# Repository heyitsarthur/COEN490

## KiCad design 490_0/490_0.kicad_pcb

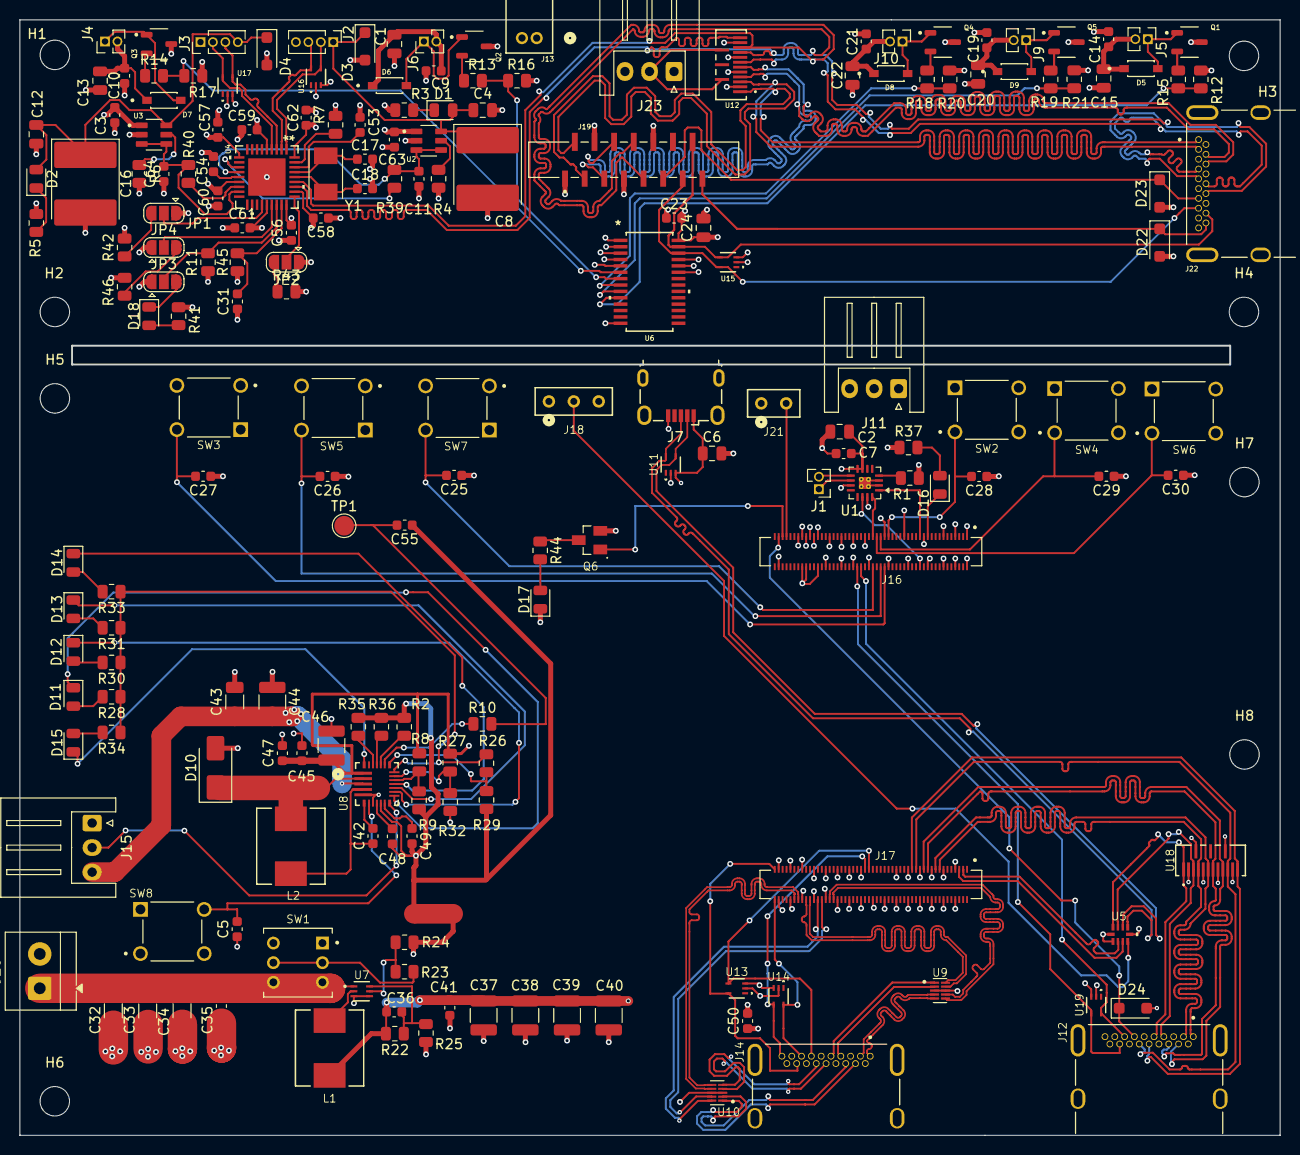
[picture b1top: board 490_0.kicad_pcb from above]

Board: 4 copper layers, 128.5 x 113.7 mm, 200 parts (0 on the bottom side), 147 nets.

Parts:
C1, C2, C4, C6, C12, C13, C15, C20, C22, C24: 10u; C_0805_2012Metric
C3, C5, C7, C9, C10, C11, C14, C19, C21, C23, C25, C26, C27, C28, C29, C30, C31, C35, C41, C42, C49, C53, C54, C55, C56, C57, C58, C59, C60, C61, C63, C64: 100n; C_0603_1608Metric
C8, C16: 120u; CP_EIA-7260-38_AVX-R_HandSolder
C17, C18, C36: 33pF; C_0603_1608Metric
C32, C33, C34: 10u; C_1206_3216Metric
C37, C38, C39, C40, C44, C46: 22u; C_1210_3225Metric
C43: 1u; C_1206_3216Metric
C45, C47, C50: 4.7u; C_0603_1608Metric
C48, C62: 1u; C_0603_1608Metric
D1, D2: LTST-C170TBKT; LED_0805_2012Metric
D3, D4: SMF5.0A; D_SOD-123F
D5, D6, D7, D8, D9: 1N4148W; SODFL3816X120N
D10: B330B-13-F; D_SMA
D11, D12, D13, D14, D16, D18: LTST-C170GKT; LED_0805_2012Metric
D15: LTST-C170YKT; LED_0805_2012Metric
D17: LTST-C170KRKT; LED_0805_2012Metric
D22, D23, D24: GSMF3.3A; D_SOD-123F
H1, H2, H3, H4, H5, H6, H7, H8: MountingHole; MountingHole_3mm
J1, J4, J5, J6, J9, J10: PAD; PinHeader_1x02_P1.27mm_Vertical
J2, J3: PAD; PinHeader_1x04_P1.27mm_Vertical
J7: 629105150521; USB_Micro-B_Wuerth_629105150521
J11, J15, J23: S3B-XH-A; JST_XH_S3B-XH-A_1x03_P2.50mm_Horizontal
J12, J14, J22: 2000-1-1-20-00-BK; CNCTECH_2000-1-1-20-00-BK
J13: S2B-ZR; CONN_S2B-ZR_JST
J16, J17: DF40HC(3.0)-100DS-0.4V(58); HIROSE_DF40C-100DS-0.4V_51_
J18: TS-103-G-A; CON3_1X3_TU_HTS_SAI - 3POS Connector
J19: SFW15S-2STE1LF
J20: YO0201500000G; TerminalBlock_4Ucon_1x02_P3.50mm_Horizontal
J21: TS-102-G-A; CON2_1X2_TU_HTS_SAI
JP1, JP2, JP3, JP4: SolderJumper-3_P1.3mm_Open_RoundedPad1.0x1.5mm
L1, L2: 2.2u; IND_SRP6540-2R2M_BRN
NT2: NetTie_2; NetTie-2_SMD_Pad2.0mm
Q1, Q2, Q3, Q4, Q5: AO3400A; SOT95P280X125-3N
Q6: BSS84; SOT95P240X120-3N
R1, R15, R16, R17, R20, R21, R23, R39, R40: 100k; R_0805_2012Metric
R2, R36: 215k; R_0805_2012Metric
R3, R5: 1k; R_0805_2012Metric
R4, R6: 20k; R_0805_2012Metric
R7: 12k; R_0805_2012Metric
R8: 76.8k; R_0805_2012Metric
R9: 24.3k; R_0805_2012Metric
R10, R26, R32, R42, R43, R45, R46: 10k; R_0805_2012Metric
R11: 330; R_0805_2012Metric
R12, R13, R14, R18, R19: 220; R_0805_2012Metric
R22: 220k; R_0805_2012Metric
R24: 30.1k; R_0805_2012Metric
R25: 30k; R_0805_2012Metric
R27: 27.4k; R_0805_2012Metric
R28, R30, R31, R33, R34, R41: 1.5k; R_0805_2012Metric
R29: 15k; R_0805_2012Metric
R35: 120k; R_0805_2012Metric
R37, R44: 470; R_0805_2012Metric
SW1: TL2230EEF140; SW_TL2230EEF140
SW2, SW3, SW4, SW5, SW6, SW7, SW8: TL1105LF160Q; SW_TL1105LF160Q
TP1: TestPoint; TestPoint_Pad_D2.0mm
U1: MAX98357A; TQFN-16-1EP_3x3mm_P0.5mm_EP1.23x1.23mm_ThermalVias
U2, U3: TPS2553DBVR; SOT95P280X145-6N_TPS2553DBVR
U4: USB2512B-I/M2; SQFN36_M2_MCH_USB2512B_I_M2
U5: TS3USB221AQRSERQ1; RSE10
U6: PCA9685; TSSOP28_SOT361-1_NXP
U7: TPS566247DRLR; SOT-5X3-6_DRL_TEX
U8: MP2639AGR-Z; IC26_MP2632BGR-Z_MNP
U9, U10: EMI8142MUTAG; SON40P220X135X50-10N_EMI8142MUTAG
U11, U13, U14, U15, U16, U17, U19: SP3003-02XTG; SOT553_LTF_SP3003_02XTG
U12, U18: TPD8S009DSMR
Y1: 24M20P2/XT324-10/10; Crystal_SMD_TXC_7A-2Pin_5x3.2mm

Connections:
+3.3V: J11.2, J12.18 (+5V), J16.78, J16.84, J16.86, J18.1, Q6.2 (S), R37.1, U5.10 (VCC), U18.13 (VCC), U18.15 (VCC), U19.3
+3.3V_GLASSES: C3.2 (-), C23.2 (-), C24.1 (+), C56.2 (-), C57.2 (-), C58.2 (-), C59.2 (-), C60.2 (-), C61.2 (-), C62.2 (-), C63.2 (-), J23.2, R41.1, R42.2, R43.2, R45.1, R46.2, U2.1 (IN), U3.1 (IN), U4.5 (VDDA33), U4.10 (VDDA33), U4.15 (VDD33), U4.23 (VDD33), U4.27 (VBUS_DET), U4.29 (VDDA33), U4.36 (VDDA33), U6.28 (VDD), U12.13 (VCC), U12.15 (VCC), U15.3
+5V: C2.1 (+), C7.2 (-), C36.2 (-), C37.2 (-), C38.2 (-), C39.2 (-), C40.2 (-), C41.2 (-), C50.1 (+), J11.3, J14.18 (+5V), J16.77, J16.79, J16.81, J16.83, J16.85, J16.87, L1.2, R1.1, R22.2, U1.7 (VDD), U1.8 (VDD), U13.3, U14.3
+5V_GLASSES: C1.1 (+), C9.2 (-), C10.2 (-), C13.1 (+), C14.2 (-), C15.1 (+), C19.2 (-), C20.1 (+), C21.2 (-), C22.1 (+), D5.1 (K), D6.1 (C), D7.1 (K), D8.1 (K), D9.1 (K), J4.2, J5.2, J6.2, J9.2, J10.2, J13.2, J23.3, U16.3, U17.3
+VBATT_7V4: C32.2 (-), C33.2 (-), C34.2 (-), C35.2 (-), J20.1, SW1.3 (C), SW1.6 (C), U7.1 (VIN)
/PCB1/PCB1-Board Connector A/CAM1_C_N: J12.12 (CK-), J17.27, U18.10 (D3+)
/PCB1/PCB1-Board Connector A/CAM1_C_P: J12.10 (CK+), J17.29, U18.12 (D3-)
/PCB1/PCB1-Board Connector A/CAM1_D0_N: J12.3 (D2-), J17.15, U18.4 (D1+)
/PCB1/PCB1-Board Connector A/CAM1_D0_P: J12.1 (D2+), J17.17, U18.6 (D1-)
/PCB1/PCB1-Board Connector A/CAM1_D1_N: J12.6 (D1-), J17.21, U18.7 (D2+)
/PCB1/PCB1-Board Connector A/CAM1_D1_P: J12.4 (D1+), J17.23, U18.9 (D2-)
/PCB1/PCB1-Board Connector A/Camera_GPIO: D24.1 (K), J12.13 (CEC), J16.97
/PCB1/PCB1-Board Connector A/HDMI0_CEC: J14.13 (CEC), J17.51, U13.4
/PCB1/PCB1-Board Connector A/HDMI0_CLK_N: J17.90, U10.6 (OUT_2-)
/PCB1/PCB1-Board Connector A/HDMI0_CLK_P: J17.88, U10.7 (OUT_2+)
/PCB1/PCB1-Board Connector A/HDMI0_HOTPLUG: J14.19 (HPD), J17.53, U14.4
/PCB1/PCB1-Board Connector A/HDMI0_SCL: J14.15 (SCL), J17.100, U14.5
/PCB1/PCB1-Board Connector A/HDMI0_SDA: J14.16 (SDA), J17.99, U13.5
/PCB1/PCB1-Board Connector A/HDMI0_TX0_N: J17.84, U9.10 (OUT_1+)
/PCB1/PCB1-Board Connector A/HDMI0_TX0_P: J17.82, U9.9 (OUT_1-)
/PCB1/PCB1-Board Connector A/HDMI0_TX1_N: J17.78, U10.10 (OUT_1+)
/PCB1/PCB1-Board Connector A/HDMI0_TX1_P: J17.76, U10.9 (OUT_1-)
/PCB1/PCB1-Board Connector A/HDMI0_TX2_N: J17.72, U9.6 (OUT_2-)
/PCB1/PCB1-Board Connector A/HDMI0_TX2_P: J17.70, U9.7 (OUT_2+)
/PCB1/PCB1-Board Connector A/PCM_CLK: J16.49, U1.16 (BCLK)
/PCB1/PCB1-Board Connector A/PCM_DOUT: J16.25, U1.1 (DIN)
/PCB1/PCB1-Board Connector A/PCM_FS: J16.26, U1.14 (LRCLK)
/PCB1/PCB1-Board Connector A/SCL1: J12.15 (SCL), J16.56, U19.5
/PCB1/PCB1-Board Connector A/SDA1: J12.16 (SDA), J16.58, U19.4
/PCB1/PCB1-Board Connector A/USB_N: J17.3, U5.7 (D-)
/PCB1/PCB1-Board Connector A/USB_P: J17.5, U5.8 (D+)
/PCB1/PCB1-Charging and Power Port + USB switch/MICROD+: J7.3 (D+), U5.1 (1D+), U11.5
/PCB1/PCB1-Charging and Power Port + USB switch/MICROD-: J7.2 (D-), U5.2 (1D-), U11.4
/PCB1/PCB1-Charging and Power Port + USB switch/USBhub_N: J12.9 (D0-), U5.4 (2D-), U18.1 (D0+)
/PCB1/PCB1-Charging and Power Port + USB switch/USBhub_P: J12.7 (D0+), U5.3 (2D+), U18.3 (D0-)
/PCB1/PCB1-HDMI/CLK+: J14.10 (CK+), U10.4 (IN_2+)
/PCB1/PCB1-HDMI/CLK-: J14.12 (CK-), U10.5 (IN_2-)
/PCB1/PCB1-HDMI/D0+: J14.7 (D0+), U9.2 (IN_1−)
/PCB1/PCB1-HDMI/D0-: J14.9 (D0-), U9.1 (IN_1+)
/PCB1/PCB1-HDMI/D1+: J14.6 (D1-), U10.2 (IN_1−)
/PCB1/PCB1-HDMI/D1-: J14.4 (D1+), U10.1 (IN_1+)
/PCB1/PCB1-HDMI/D2+: J14.3 (D2-), U9.4 (IN_2+)
/PCB1/PCB1-HDMI/D2-: J14.1 (D2+), U9.5 (IN_2-)
/PCB2/CK+: J19.9, J22.7 (D0+), J22.10 (CK+), U4.31 (USBDP_UP), U12.7 (D2+), U12.10 (D3+)
/PCB2/CK-: J19.8, J22.9 (D0-), J22.12 (CK-), U4.30 (USBDM_UP), U12.9 (D2-), U12.12 (D3-)
/PCB2/D0+: J19.3, J22.1 (D2+), U12.1 (D0+)
/PCB2/D0-: J19.2, J22.3 (D2-), U12.3 (D0-)
/PCB2/D1+: J19.6, J22.4 (D1+), U12.4 (D1+)
/PCB2/D1-: J19.5, J22.6 (D1-), U12.6 (D1-)
/PCB2/PCB2-PWM and Motors/I2C_SCL: J19.13, J22.15 (SCL), U6.26 (SCL), U15.5
/PCB2/PCB2-PWM and Motors/I2C_SDA: J19.14, J22.16 (SDA), U6.27 (SDA), U15.4
/PCB2/PCB2-PWM and Motors/PWM0: R14.2, R17.1, U6.6 (PWM0)
/PCB2/PCB2-PWM and Motors/PWM1: R13.2, R16.1, U6.7 (PWM1)
/PCB2/PCB2-PWM and Motors/PWM2: R18.2, R20.1, U6.8 (PWM2)
/PCB2/PCB2-PWM and Motors/PWM3: R19.2, R21.1, U6.9 (PWM3)
/PCB2/PCB2-PWM and Motors/PWM4: R12.2, R15.1, U6.10 (PWM4)
/PCB2/PCB2-USB 2.0 Bridge/D1+: J2.3, U4.2 (USBDP_DN1/PRT_DIS_P1), U16.5
/PCB2/PCB2-USB 2.0 Bridge/D1-: J2.2, U4.1 (USBDM_DN1/PRT_DIS_M1), U16.4
/PCB2/PCB2-USB 2.0 Bridge/D2+: J3.2, U4.4 (USBDP_DN2/PRT_DIS_P2), U17.5
/PCB2/PCB2-USB 2.0 Bridge/D2-: J3.3, U4.3 (USBDM_DN2/PRT_DIS_M2), U17.4
/PCB2/PCB2-USB 2.0 Bridge/EN1: R39.2, U4.12 (PRTPWR1/BC_EN1)
/PCB2/PCB2-USB 2.0 Bridge/EN2: R40.2, U4.16 (PRTPWR2/BC_EN2)
/PCB2/PCB2-USB 2.0 Bridge/nOCS1: C11.2 (-), R39.1, U2.3 (EN), U2.4 (~FAULT), U4.13 (OCS_N1)
/PCB2/PCB2-USB 2.0 Bridge/nOCS2: C64.2 (-), R40.1, U3.3 (EN), U3.4 (~FAULT), U4.17 (OCS_N2)
GND: C2.2 (-), C5.1 (+), C6.2 (-), C7.1 (+), C25.1 (+), C26.1 (+), C27.1 (+), C28.1 (+), C29.1 (+), C30.1 (+), C32.1 (+), C33.1 (+), C34.1 (+), C35.1 (+), C37.1 (+), C38.1 (+), C39.1 (+), C40.1 (+), C41.1 (+), C43.2 (-), C44.1 (+), C45.2 (-), C46.2 (-), C47.2 (-), C48.2 (-), C49.2 (-), C50.2 (-), C55.1 (+), D10.2 (A), D17.1 (K), D24.2 (A), J7.5 (GND), J7.6 (Shield), J11.1, J12.2 (D2S), J12.5 (D1S), J12.8 (D0S), J12.11 (CKS), J12.17 (GND), J12.SH1, J12.SH2, J12.SH3, J12.SH4, J14.2 (D2S), J14.5 (D1S), J14.8 (D0S), J14.11 (CKS), J14.17 (GND), J14.SH1, J14.SH2, J14.SH3, J14.SH4, J15.1, J16.1, J16.2, J16.7, J16.8, J16.13, J16.14, J16.22, J16.23, J16.32, J16.33, J16.42, J16.43, J16.52, J16.53, J16.59, J16.60, J16.65, J16.66, J16.71, J16.74, J16.98, J17.7, J17.8, J17.13, J17.14, J17.19, J17.20, J17.25, J17.26, J17.31, J17.32, J17.37, J17.38, J17.44, J17.50, J17.55, J17.56, J17.61, J17.62, J17.67, J17.68, J17.73, J17.74, J17.79, J17.80, J17.85, J17.86, J17.91, J17.92, J17.97, J17.98, J18.3, J20.2, J21.1, NT2.1, NT2.2, R2.1, R9.1, R24.1, R25.1, R29.1, R32.2, R35.1, R36.1, SW2.3, SW3.2, SW4.3, SW5.2, SW6.3, SW7.2, SW8.1, U1.2 (GAIN_SLOT), U1.3 (GND), U1.11 (GND), U1.15 (GND), U1.17 (PAD), U5.5 (GND), U5.6 (*OE), U7.3 (GND), U7.4 (AGND), U8.5 (PGND), U8.8 (MODE), U8.10 (AGND), U9.3 (VN), U9.8 (VN__1), U10.3 (VN), U10.8 (VN__1), U11.2, U13.2, U14.2, U18.2 (GND), U18.5 (GND), U18.8 (GND), U18.11 (GND), U19.2
GND_GLASSES: C1.2 (-), C3.1 (+), C4.2 (-), C8.2, C9.1 (+), C10.1 (+), C11.1 (+), C12.2 (-), C13.2 (-), C14.1 (+), C15.2 (-), C16.2, C17.2 (-), C18.2 (-), C19.1 (+), C20.2 (-), C21.1 (+), C22.2 (-), C23.1 (+), C24.2 (-), C31.1 (+), C53.1 (+), C54.1 (+), C56.1 (+), C57.1 (+), C58.1 (+), C59.1 (+), C60.1 (+), C61.1 (+), C62.1 (+), C63.1 (+), C64.1 (+), D3.2 (A), D4.2 (A), D22.2 (A), D23.2 (A), J2.4, J3.1, J13.1, J19.1, J19.4, J19.7, J19.10, J22.2 (D2S), J22.5 (D1S), J22.8 (D0S), J22.11 (CKS), J22.17 (GND), J22.SH1, J22.SH2, J22.SH3, J22.SH4, J23.1, JP1.1 (A), JP2.1 (A), JP3.1 (A), JP4.1 (A), Q1.3 (S), Q2.3 (S), Q3.3 (S), Q4.3 (S), Q5.3 (S), R3.1, R4.2, R5.1, R6.2, R7.2, R11.1, R15.2, R16.2, R17.2, R20.2, R21.2, U2.2 (GND), U3.2 (GND), U4.37 (VSS), U6.1 (A0), U6.2 (A1), U6.3 (A2), U6.4 (A3), U6.5 (A4), U6.14 (GND), U6.23 (#OE), U6.24 (A5), U6.25 (EXTCLK), U12.2 (GND), U12.5 (GND), U12.8 (GND), U12.11 (GND), U15.2, U16.2, U17.2
unnamed: C5.2 (-), SW8.3, U8.7 (PB)
unnamed: C17.1 (+), U4.33 (XTALIN/CLKIN), Y1.1
unnamed: C18.1 (+), U4.32 (XTALOUT), Y1.2
unnamed: C25.2 (-), J16.50, SW7.3
unnamed: C26.2 (-), J16.46, SW5.3
unnamed: C27.2 (-), J16.44, SW3.3
unnamed: C28.2 (-), J16.41, SW2.2
unnamed: C29.2 (-), J16.45, SW4.2
unnamed: C30.2 (-), J16.47, SW6.2
unnamed: C31.2 (-), R45.2, U4.26 (RESET_N)
unnamed: C36.1 (+), R22.1, R25.2, U7.6 (FB)
unnamed: C42.1 (+), U8.6 (BST)
unnamed: C42.2 (-), L2.1, U8.4 (SW)
unnamed: C43.1 (+), C44.2 (-), J15.3, U8.3 (VH)
unnamed: C48.1 (+), U8.9 (VCC)
unnamed: C49.1 (+), U8.11 (TMR)
unnamed: C53.2 (-), U4.34 (PLLFILT)
unnamed: C54.2 (-), U4.14 (CRFILT)
unnamed: C55.2 (-), R10.2, TP1.1
unnamed: D1.1 (K), R3.2
unnamed: D2.1 (K), R5.2
unnamed: D5.2 (A), J5.1, Q1.1 (D)
unnamed: D6.2 (A), J6.1, Q2.1 (D)
unnamed: D7.2 (A), J4.1, Q3.1 (D)
unnamed: D8.2 (A), J10.1, Q4.1 (D)
unnamed: D9.2 (A), J9.1, Q5.1 (D)
unnamed: D10.1 (K), L2.2, U8.2 (LX)
unnamed: D11.2 (A), R28.2
unnamed: D11.1 (K), U8.13 (LED1)
unnamed: D12.2 (A), R30.2
unnamed: D12.1 (K), U8.14 (LED2)
unnamed: D13.2 (A), R31.2
unnamed: D13.1 (K), U8.15 (LED3)
unnamed: D14.2 (A), R33.2
unnamed: D14.1 (K), U8.16 (LED4)
unnamed: D15.2 (A), R34.2
unnamed: D15.1 (K), U8.26 (CHG)
unnamed: D16.2 (A), R37.2
unnamed: D16.1 (K), J16.21
unnamed: D17.2 (A), R44.2
unnamed: D18.2 (A), R41.2
unnamed: D18.1 (K), JP3.3 (B)
unnamed: D22.1 (K), J19.15, J22.18 (+5V)
unnamed: D23.1 (K), J19.11, J22.13 (CEC)
unnamed: J1.1, U1.10 (OUTN)
unnamed: J1.2, U1.9 (OUTP)
unnamed: J15.2, U8.12 (MID)
unnamed: J18.2, U5.9 (S)
unnamed: J16.93, J21.2
unnamed: JP1.3 (B), R42.1
unnamed: JP1.2 (C), U4.22 (SDA/SMBDATA/NON_REM1)
unnamed: JP2.3 (B), R43.1
unnamed: JP2.2 (C), U4.28 (SUSP_IN/LOCAL_PWR/NON_REM0)
unnamed: JP3.2 (C), R11.2, U4.25 (HS_IND/CFG_SEL1)
unnamed: JP4.3 (B), R46.1
unnamed: JP4.2 (C), U4.24 (SCL/SMBCLK/CFG_SEL0)
unnamed: Q1.2 (G), R12.1
unnamed: Q2.2 (G), R13.1
unnamed: Q3.2 (G), R14.1
unnamed: Q4.2 (G), R18.1
unnamed: Q5.2 (G), R19.1
unnamed: Q6.3 (D), R44.1
unnamed: J16.95, Q6.1 (G)
unnamed: R23.2, SW1.2 (B), SW1.5 (B)
unnamed: R1.2, U1.4 (~SD_MODE)
unnamed: R4.1, U2.5 (ILIM)
unnamed: R6.1, U3.5 (ILIM)
unnamed: R7.1, U4.35 (RBIAS)
unnamed: R23.1, R24.2, U7.5 (EN)
unnamed: L1.1, U7.2 (SW)
unnamed: R8.1, R9.2, U8.17 (FB)
unnamed: R10.1, U8.21 (IB)
unnamed: R35.2, U8.24 (ILIM)
unnamed: R36.2, U8.23 (ISET)
unnamed: R26.1, R29.2, U8.20 (NTC)
unnamed: R2.2, U8.22 (OLIM)
unnamed: R27.2, R32.1, U8.18 (VLIM)
unnamed: R26.2, R28.1, R30.1, R31.1, R33.1, R34.1, U8.19 (VNTC)
VBUS1: C4.1 (+), C8.1, D1.2 (A), D3.1 (K), J2.1, U2.6 (OUT)
VBUS2: C12.1 (+), C16.1, D2.2 (A), D4.1 (K), J3.4, U3.6 (OUT)
VBUS_5V: C6.1 (+), C45.1 (+), C46.1 (+), C47.1 (+), J7.1 (VBUS), R8.2, R27.1, U8.1 (VL), U11.3

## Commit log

2025-11-20 Setup
2025-11-20 USB and POWER
2025-11-20 Startted power
2025-11-22 Added USB hub
2025-11-22 Added speakers, motors and started HDMI
2025-11-22 Power Supply
2025-11-23 Phase 2
2025-11-23 Added zip file of datasheets
2025-11-27 Small update
2025-11-27 Changed charging circuit
2025-11-27 Finished USB C charger (3.3 and 5V)
    Added buck converter after the charging IC for 3.3 and 5V outputs.
2025-11-30 Arranged schematic
    Added sheets (as in the phase 2 presentation)
2025-11-30 US letter format
2025-12-01 Changed some local labels to the right format
2025-12-01 Fixed buttons
2025-12-01 changed local labels
    Do not use global labels if its only used in a single sheet
2025-12-01 Added debouncing to the buttons
2025-12-12 Minor fixes
2025-12-12 LEDs for charger
2025-12-12 Charging circuit updates
    NTC thermal resistor
    Changed some TBD values for resistors and capacitors
2025-12-13 Changed the camera connectors
    - Added 2 and 4 lane MIPI 22 lane connectors
    - Added digikey link to a good type
2026-01-15 Minor updates + USB 2.0
2026-01-15 Minor updates
2026-01-19 USB2.0
    Added USB2.0 circuit
2026-01-19 Updated box diagram
2026-01-22 BOM + ESD replacement for HDMI
    Started BOM and changed ESD chips that were obsolete. Also added 2 pin connectors
2026-01-22 small commit
2026-01-23 Added another button + address fix
2026-01-27 Updated block diagram
2026-01-27 changed PCB block diagram
2026-01-28 Changed PCB block dagram and layout
2026-01-29 Schematic layout update
    - applied hierarchical labels
    - cleaned up the schematic
    - finalized CM4 connections
    - checked cm4 connections
2026-01-30 Cleaned up global labels
    TO DO: power chip change
2026-02-02 Updated power circuit
    We now have a 2 cell battery
    Chip provides 4A/5V source
2026-02-03 Finished power circuit
2026-02-05 Power + BOM update
2026-02-05 finished BOM
2026-02-06 Changed buck converter chip
2026-02-06 Updated the schematic
2026-02-09 Implemented Dmitry comments
2026-02-11 Final Fixes
2026-02-11 USB hub fix
2026-02-17 Implemented Dmitry recommendations
2026-02-20 Added datasheets and footprints to repo
2026-02-25 Implemented suggestions
    notes on schematics:
    Overall: Schematics needs to be improved, more compact and cleaner
    =========================
    I) on root page (page 1):
    overall: needs a bit of clean up of the diagram
    1. the diagram shows pcb3 and pcb1, but no pcb2, it is probably outdated and therefore might have errors in it, fix it to the latest version and rename things to reflect what it actually is. Also try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
2026-02-26 FFC to HDMI change
2026-02-27 Footprints
    Required library of custom footprints for the PCB design
2026-02-27 Reviewed BOM
    - changed some capacitors to a more fitting voltage rating
2026-02-27 Footprint Update
    1st half of footprints updated
2026-02-27 Footprint Update #2
    All footprints except for the capacitors have been attributed
2026-02-27 Archive update
    .zip files update for archive purposes
2026-03-03 ToF power routing
2026-03-03 Changed 8conn and BOM update
2026-03-03 PCB Trial Update
2026-03-03 LED names + 5V routing through ESD + renamed ESD chips to "U"
2026-03-03 Renamed crystal + BOM update
2026-03-03 Updated schematic PDF
2026-03-03 Changed ESD chip for HDMI
2026-03-03 Fixed capacitor symbols
2026-03-04 PCB Jumpstart
2026-03-04 Post-Dmitry Changes
2026-03-04 Added seperate ground for PWM motors
2026-03-04 Updated to 10 pin connector
2026-03-04 Added 10 pin connector footprint
2026-03-04 Changed footprints for pad connectors (for soldered components)
2026-03-04 Changed footprint for R4 and R6 to SMD
2026-03-04 Changed capacitor sizes
    🟢 Group 1: 100% Safe to Shrink to 0603These capacitors handle logic-level decoupling or high-frequency filtering on your 3.3V and 5V lines. Because the capacitance values are low (1µF or less), an 06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
2026-03-04 Assigned capacitor footprints
2026-03-04 Changed all the resistors to 0805 size
2026-03-04 Scheamtic update
2026-03-05 PCB_2 Design Initialization
2026-03-05 Added button debouncing
2026-03-05 changed power and ground symbols for glasses
2026-03-05 Generated BOM
2026-03-05 Changed audio chip to 5V
    It might pull to omuch if we ue the raspberry's 3.3V rail
2026-03-05 ERC check fix
2026-03-05 Updated scheamitc in folder
2026-03-05 Added side B for SW1
2026-03-05 switch fix
2026-03-05 Rerouted + external coponents update
2026-03-05 March 3rd
2026-03-06 PCB_Glasses Implementation
2026-03-06 15 pin connector mirrored
2026-03-06 Changed connector 15 pin
2026-03-07 Fixed button debouncing
2026-03-09 Git PCB Fix
2026-03-09 small push
2026-03-09 Some changes
2026-03-09 Placed 100 pin connectors
2026-03-09 Button debouncing fix
2026-03-10 started routing up to HDMI ESD impedance matching
2026-03-10 HDMI to ESD diff pairs routed
2026-03-10 Finished ESD diff pairs routing
2026-03-10 Changed microHDMI to normal HDMI because of the footprint
2026-03-10 Tuesday March 10th: 13:25
2026-03-10 Routing ESD to 100 pin connector
2026-03-10 Tuesday Match 10th: 14:45
    Conflicting skew fix
2026-03-10 Final push
2026-03-10 PCB merged, now schematic
2026-03-10 All merged up! 03-10
2026-03-10 Wired up screen HDMI to 100pin
2026-03-10 Still need to wire diff pairs from FFC HDMI
2026-03-11 Speaker circuit
2026-03-11 Routed the FFC HDMI to 100conn
2026-03-11 added a few grounds around signal vias
2026-03-11 Fixed SP3003-02XTG continuity
2026-03-11 Place CM4 footprint, starting to reroute everything
2026-03-11 Removed ports from below the CM4
2026-03-11 same
2026-03-11 Eliminated some acidtraps
2026-03-11 Connected microUSB port
2026-03-12 Routed j18
2026-03-12 Changed pin assignment for the buttons on PCB1 in the schematic
2026-03-12 Routed buttons
2026-03-12 Routed LED for the 100con
2026-03-12 Routed other LED
2026-03-12 almost finished charging
2026-03-12 Routed the 7.4V line in a weird way
2026-03-12 Charging circuit finished
2026-03-12 Routing done, nned to fit into PCB
2026-03-12 merged with Ardi (PCB glasses)
2026-03-12 Merged schematic
2026-03-12 Thicker copper pour
2026-03-12 added terdrop for 5Vbus
2026-03-12 Fixing vias and acidtraps
2026-03-13 set the PCB size to match glasses
2026-03-13 Finished PCB1 routing
2026-03-13 Ground shields
2026-03-13 Diif pair fix
2026-03-13 Merged with Ardi
2026-03-13 merged
2026-03-13 Changed the HDMI connections on glasses
2026-03-13 Friday, March 13th: PCB Planes Addition
2026-03-13 FInished routing
2026-03-13 merged up
2026-03-13 merge
2026-03-20 Friday, March 20th: PCB Final for BOM
2026-03-22 Updated BOM
2026-04-03 Final commit
